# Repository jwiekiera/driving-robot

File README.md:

# Driving Robot

Project description: The project aims to create a mobile robot. The device can overcome obstacles detected by sensors (e.g., walls, objects on the ground). The robot moves using mechanical wheels.

* (20.10.2023) **Version 0.1**: Project work initiation
* (20.12.2023) **Version 0.2:** Placement of components on the platform
* (27.12.2023) **Version 0.3:** Completion of project implementation on the breadboard
* (09.02.2024) **Version 0.4:** Soldering the components together
* (13.02.2024) **Version 1.0:** Final version of the project

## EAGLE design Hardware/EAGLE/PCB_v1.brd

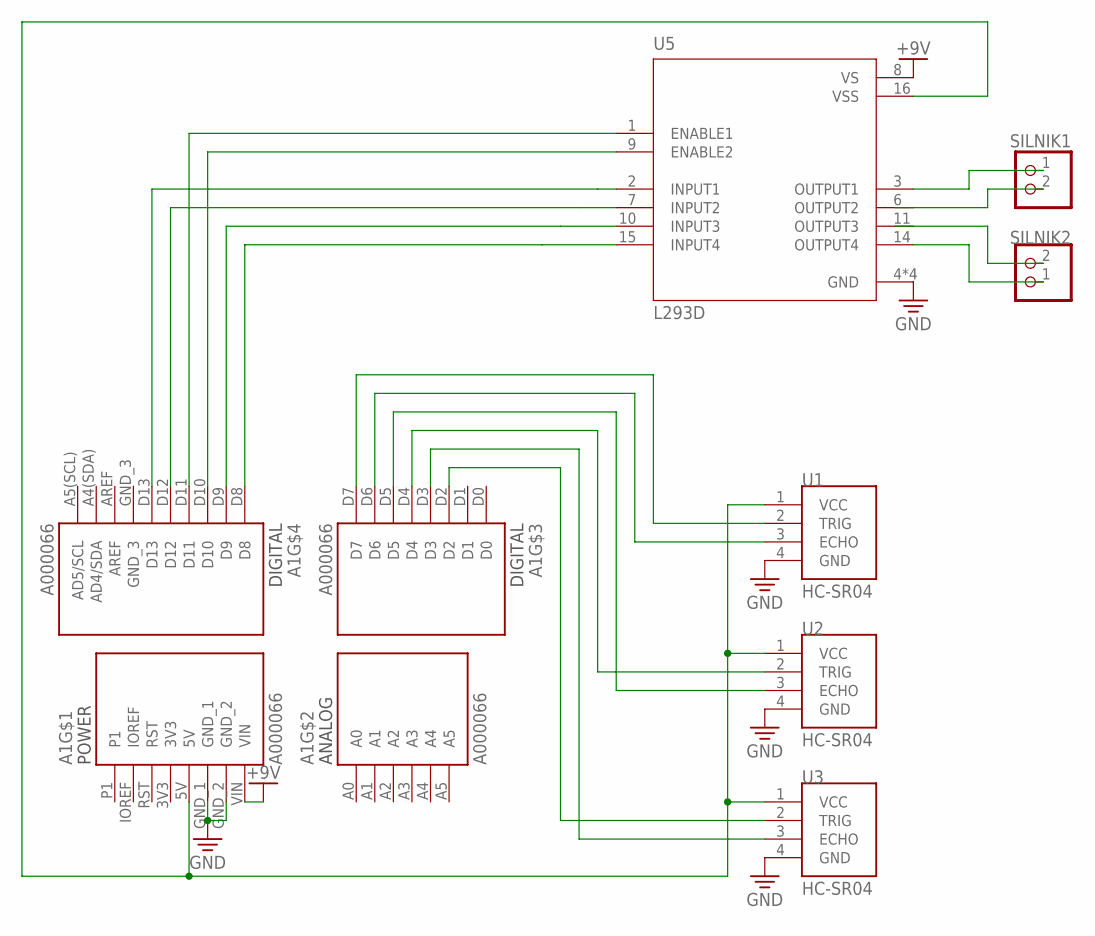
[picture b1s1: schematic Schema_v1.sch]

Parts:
A1: A000066; ARDUINO_A000066
SILNIK1, SILNIK2: PINHD-1X2/90; 1X02/90
U1, U2, U3: HC-SR04; XCVR_HC-SR04
U5: L293D; DIP880W50P254L2000H510Q16

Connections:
3V3: A1.3V3
+9V: A1.VIN, U5.8 (VS)
GND: A1.GND_1, A1.GND_2, U1.4 (GND), U2.4 (GND), U3.4 (GND), U5.4 (GND), U5.5 (GND), U5.12 (GND), U5.13 (GND)
GND_3: A1.GND_3
unnamed: A1.D2, U3.2 (TRIG)
unnamed: SILNIK1.1, U5.3 (OUTPUT1)
unnamed: SILNIK1.2, U5.6 (OUTPUT2)
unnamed: A1.D8, U5.15 (INPUT4)
unnamed: SILNIK2.2, U5.11 (OUTPUT3)
unnamed: SILNIK2.1, U5.14 (OUTPUT4)
unnamed: A1.D11, U5.1 (ENABLE1)
unnamed: A1.5V, U1.1 (VCC), U2.1 (VCC), U3.1 (VCC), U5.16 (VSS)
unnamed: A1.D9, U5.10 (INPUT3)
unnamed: A1.D12, U5.7 (INPUT2)
unnamed: A1.D10, U5.9 (ENABLE2)
unnamed: A1.D13, U5.2 (INPUT1)
unnamed: A1.D4, U2.2 (TRIG)
unnamed: A1.D5, U2.3 (ECHO)
unnamed: A1.D3, U3.3 (ECHO)
unnamed: A1.D6, U1.3 (ECHO)
unnamed: A1.D7, U1.2 (TRIG)

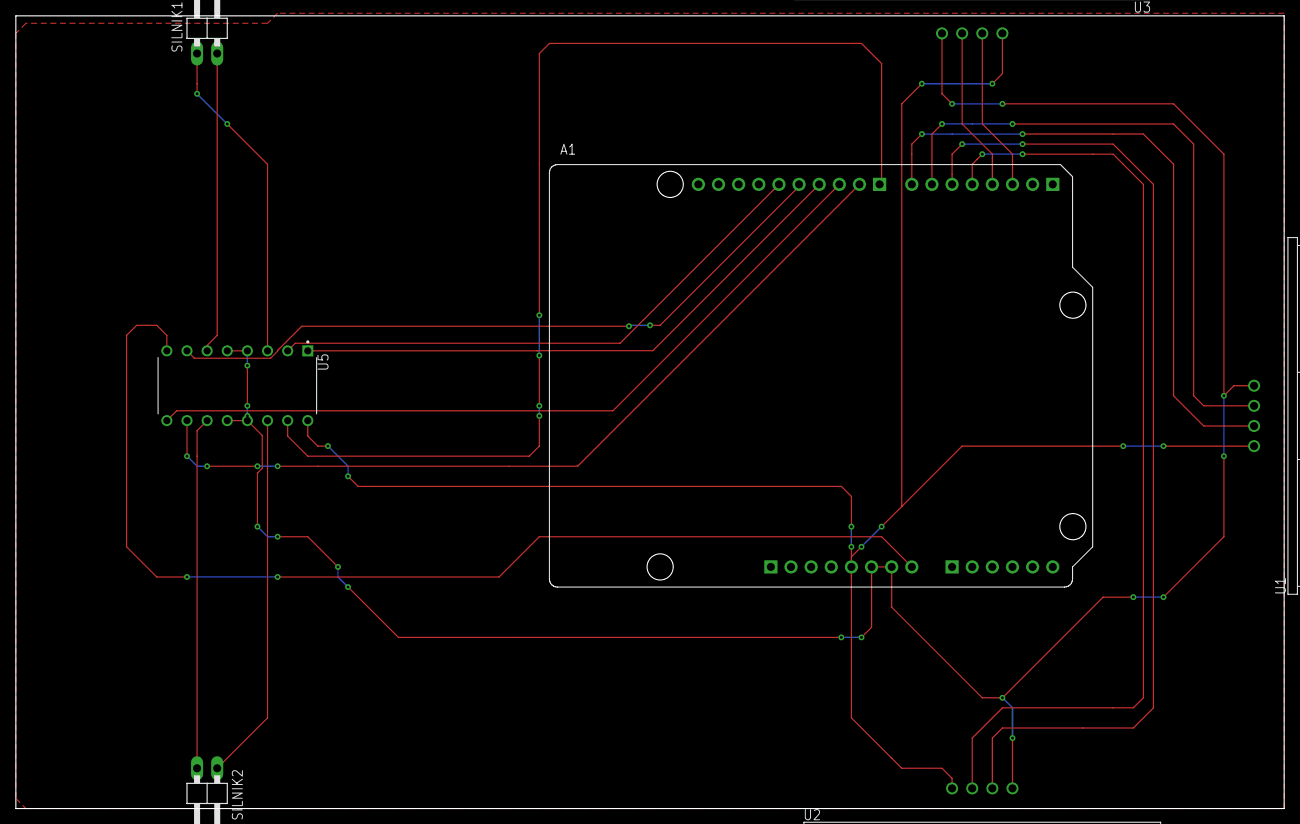
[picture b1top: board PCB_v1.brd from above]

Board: 2 copper layers, 160.0 x 100.0 mm, 7 parts (0 on the bottom side), 19 nets.

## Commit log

2024-05-29 Adding documentation, software and hardware
2024-05-29 Renaming folders
2024-05-29 Renaming files names
2024-05-29 Adding img folder
